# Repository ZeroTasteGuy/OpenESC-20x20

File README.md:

# OpenESC-20x20

A 4-in-1 sensorless BLDC ESC for the **20 x 20 mm** FPV stack hole pattern: four
independent motor controllers, each with its own MCU, gate driver and six
MOSFETs, running AM32 and taking DShot over a standard 8-pin connector.

> **Status: placement only.** All parts are placed, but there is **no copper and
> no routing**. The board has not been routed, fabricated or tested. Do not
> order it. See [Known issues](#known-issues).

3D views: [top](hardware-20x20/images/20x20-3d-top.png),
[bottom](hardware-20x20/images/20x20-3d-bottom.png).

This is a new PCB layout of the circuit from
[OpenDrone-hw/OpenESC-30x30](https://github.com/OpenDrone-hw/OpenESC-30x30)
(CERN-OHL-S-2.0, maintainer [@Just4Stan](https://github.com/Just4Stan)). The
outline and layout are new, and this board **does not include the current-sense
circuit** (see below); the schematic was edited to match. It is not an official
OpenDrone or Incutec release and is not covered by the upstream OSHWA
certification.

## What changed from the 30x30

| | 30x30 (upstream) | 20x20 (this layout) |
|---|---|---|
| Mounting holes | 30.5 mm pattern | 20 x 20 mm, 4 mm unplated, no copper ring |
| Board size | 30.5 mm class | about 35 x 42 mm including battery tab |
| Layers / copper | 6 layers, 1.6 mm, 2 oz outer / 1 oz inner | same (rules in `4in1.kicad_pro` and `4in1.kicad_dru`) |
| Motor pads | per upstream | corner groups, 3 pads per motor, no notch mid-edge |
| MOSFETs | 24 | 24, as 12 stacked pairs (high side top, low side bottom) |
| Bulk ceramic 1206 | 52 | **28**, on top near the MOSFETs |
| Battery pads | per upstream | two castellated pads on a tab, 4 mm wide x 1.5 mm deep |
| MCU, drivers, critical passives | per upstream | bottom side |
| Programming pads | per upstream | 2.54 mm pitch with hand-rework clearance |
| Current sense | INA186 + 2 shunts, board level | **not on this board** |

Fewer bulk capacitors means less local ripple filtering; install the 470 uF 50 V
electrolytic on the battery leads. Current capacity of this layout is **not**
validated; four channels at 60 A through a board this size is not realistic. See
[hardware-20x20/docs/DESIGN-NOTES.md](hardware-20x20/docs/DESIGN-NOTES.md).

## Specifications (circuit, as upstream)

| | |
|---|---|
| Firmware | AM32 |
| ESC protocol | DShot, bidirectional |
| Telemetry | Extended DShot |
| Input | 2-8S LiPo (6.0-33.6 V) |
| BEC | None |
| Rated current | 60 A / channel in the 30x30 design; **not established for this layout** |

## Architecture

Four independent channels share one power input and one connector. Per channel:
an **AT32F421G8U7** (Cortex-M4, QFN-28) drives an **NSG2065Q** three-phase
half-bridge gate driver, which drives six **SP40N01GHNK** MOSFETs, two per
phase. One channel is drawn once in `ESC.kicad_sch` and instantiated four times.

**There is no current sensing on this board.** The upstream design has a board-level
INA186A3IDCKR across two 0.2 mOhm shunts, reported as `/CURR`. That circuit is
not placed here and was removed from the schematic: U12, Rsense1, Rsense2, R89,
R90, C40, C41, C42, C94 and R73. No per-phase shunts were added either. The
battery pad (U3 pin 1) now connects straight to `+BATT`. `/CURR` (connector pin 3)
is kept as a net but is not driven.

## Power

```
Battery + (2S-8S) ─► +BATT
+BATT ─┬─► MOSFET drains, motor phases
       └─► LMR54406DBVR buck ─► +10V ─┬─► 4x gate driver
                                      └─► TLV76733DRVR ─► +3V3 ─► 4x MCU
```

## Key parts

| Function | Ref | Part | LCSC | Note |
|---|---|---|---|---|
| Motor MCU, x4 | U2, U5, U7, U9 | AT32F421G8U7, QFN-28 | C2765098 | One per channel |
| Gate driver, x4 | U4, U6, U8, U10 | NSG2065Q, QFN-24 | C41414478 | Standard footprint, alternatives exist |
| Power MOSFET, x24 | Q1-Q24 | SP40N01GHNK, PDFN-8L 5x6 | C22385416 | 40 V, 6 per channel; standard 5x6 DFN footprint |
| Buck | U13 | LMR54406DBVR, SOT-23-6 | C5219316 | 1.1 MHz, 0.6 A; FB 115k/10k against 0.8 V for 10.0 V out |
| Buck inductor | U14 | FTC160808S4R7MBCA | C46594347 | 4.7 uH |
| LDO | U15 | TLV76733DRVR, WSON-6 | C2848334 | +10 V to +3V3 |
| Connector | J1 | SM08B-SRSS-TB, JST SH 8-pin | C160407 | Also broken out as castellated pads |
| Bulk electrolytic | / | 470 uF 50 V | / | Installed by the user on the battery leads |
| Bulk ceramic | see PCB | 4.7 uF 1206, X5R 50 V | C380366 | 28 fitted on this layout |

## Connectors and I/O

Betaflight standard 8-pin:

| Pin | Net | Function |
|---|---|---|
| 1 | +BATT | Battery positive |
| 2 | GND | Ground |
| 3 | /CURR | Current sense output; **not driven on this board** (no INA186 fitted) |
| 4 | unconnected | See below |
| 5 | /M1 | DShot, channel 1 |
| 6 | /M2 | DShot, channel 2 |
| 7 | /M3 | DShot, channel 3 |
| 8 | /M4 | DShot, channel 4 |

Pin 4 is the dedicated telemetry pin in the Betaflight 8-pin standard and is
intentionally left unconnected: ESC to FC telemetry rides the motor signal lines
over bidirectional extended DShot instead.

## Layout rules

Bulk decoupling on +BATT and GND exists on the PCB without matching schematic
symbols. That is a deliberate board-only bank. Do not run update-from-schematic
without checking what it would delete.

## Firmware

[AM32](https://github.com/am32-firmware/AM32). Load the bootloader
(`AM32_F421_BOOTLOADER_PB4_V19.hex`) first with an ST-LINK, then flash and
configure the firmware in-browser at [am32.ca](https://am32.ca). Works with
Betaflight and any other DShot-capable flight controller.

## Repository

| | |
|---|---|
| Designed in | KiCad 10 |
| KiCad project | `hardware-20x20/4in1.kicad_pro` (name kept from upstream) |
| Schematics | `hardware-20x20/4in1.kicad_sch` (power, connectors, board block U3, castellated strip J2) plus `ESC.kicad_sch` (one channel, instantiated 4x, unchanged from upstream) |
| Board | `hardware-20x20/4in1.kicad_pcb`, 6 layers, 1.6 mm, 2 oz outer / 1 oz inner copper |
| Board setup | 0.09 mm clearance and track, 0.16 mm on outer layers (2 oz), via 0.35 on 0.20 drill |
| Design rules | `hardware-20x20/4in1.kicad_dru` |
| Local libraries | `components.kicad_sym`, `4in1ESC-30x30.pretty/`, `4in1ESC-30x30.3dshapes/` (only the models in use), inherited from upstream |
| Fab config | `hardware-20x20/fabrication-toolkit-options.json` |
| Renders | `hardware-20x20/images/` |
| Design notes | `hardware-20x20/docs/DESIGN-NOTES.md` |
| Last DRC | `hardware-20x20/docs/drc-v15-placement.json` |
| Placement scripts | `hardware-20x20/tools/` (provenance only, see its README) |
| License | CERN-OHL-S-2.0, see [LICENSE](LICENSE) |

## Checks

```sh
kicad-cli sch erc hardware-20x20/4in1.kicad_sch
kicad-cli pcb drc --schematic-parity --refill-zones hardware-20x20/4in1.kicad_pcb
```

Last DRC run (`docs/drc-v15-placement.json`, without schematic parity): no
clearance or annular-ring errors after the castellated pad fix (the project has
`copper_edge_clearance` set to ignore; with it on, 4 hits remain on the battery
tab, see `hardware-20x20/docs/DESIGN-NOTES.md`); 29
`lib_footprint_mismatch` (to be cleared by re-saving footprints from KiCad
against the local library); 472 unconnected items because nothing is routed.

With schematic parity and ERC (KiCad 10, run on this schematic and board):

- Parity: every schematic part is on the board, and J2 matches except for its
  value and BOM flag (see Known issues). 25 footprints are
  board-only (the CB bulk caps, kept board-only as upstream does). 16
  `net_conflict` notes on IC pads and a J2 pad 4 net name are inherited from
  upstream and the board's footprints. About 146 field mismatches are metadata
  only (Manufacturer fields blank on the board).
- ERC: 18 `pin_not_driven` errors (was 24 upstream) and 4
  `power_pin_not_driven` (was 3). Two of those four appeared because the removed
  U3 power-output pins no longer drive `+BATT` and `GND`; adding a PWR_FLAG on
  each net clears them.

KiCad files cannot be merged. Close KiCad before any scripted write to a KiCad
file, and do not text-edit `.kicad_sch`, `.kicad_pcb` or `.kicad_dru`.

## Known issues

- **Schematic edits to finish.** Add a PWR_FLAG on `+BATT` and `GND` to clear two
  new ERC errors, and set J2's value to "Castellated FC pads" with Exclude from
  BOM ticked so it matches the board footprint exactly.
- **No current sensing.** Removed on purpose (see Architecture). The ESC reports no
  current telemetry; `/CURR` is undriven.
- No copper, planes, vias or tracks. Routing, power-plane design and a current
  and thermal check are all still to do.
- The castellated pads need the fab to accept half-plated holes of this size.
- Some small parts sit in tight clusters (0.2 to 0.3 mm gaps). An earlier
  routing attempt on a related layout failed mostly on boxed-in pads, so expect
  to spread parts or route by hand.
- Silkscreen text may still carry upstream naming; review before any fab export.

## Revisions

| Rev | Date | Change |
|---|---|---|
| v15 | 2026-10-08 | Placement only: 28 bulk caps with fab-safe spacing, battery castellation pads run to the edge, J2 silk labels 1.0 mm. No copper. |
| v15a | 2026-10-08 | Castellated motor and signal pads widened to 5 mm (clears the annular-width DRC errors). Schematic matched to the board: current-sense circuit removed, castellated strip J2 added, U3 board block redrawn as the real outline with only the pins that have pads. |

Upstream revision history (30x30 Rev1 to Rev3.3) is in the
[OpenESC-30x30 repository](https://github.com/OpenDrone-hw/OpenESC-30x30).

## Credit and licence

CERN-OHL-S-2.0, same as upstream. Original circuit and 30x30 design by the
OpenDrone / Incutec team, maintainer @Just4Stan. The 20x20 board layout is a
modified version; changes are limited to PCB outline and placement as described
above. Upstream branding, badges and certification do not carry over to this
layout.

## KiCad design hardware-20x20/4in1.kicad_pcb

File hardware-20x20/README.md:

# OpenESC 20x20 layout (derivative of OpenESC-30x30)

An alternative PCB layout of the OpenESC-30x30 4-in-1 sensorless BLDC ESC for the
**20 x 20 mm** FPV stack hole pattern. The circuit is the upstream circuit; only
the board is new.

> **Status: placement only.** All parts are placed, but there is **no copper and
> no routing**. The board has not been routed, fabricated or tested. Do not order
> it. See [Known issues](#known-issues).

Derived from [OpenDrone-hw/OpenESC-30x30](https://github.com/OpenDrone-hw/OpenESC-30x30)
(CERN-OHL-S-2.0). This is not an official OpenDrone or Incutec release and is not
covered by the upstream OSHWA certification.

3D views: [top](images/20x20-3d-top.png), [bottom](images/20x20-3d-bottom.png).

## What is the same as the 30x30

Schematics (`4in1.kicad_sch`, `ESC.kicad_sch`), symbols, nets, parts and the
design rules file are **byte-identical** to `../hardware/`. Nothing in the circuit
changed: four AT32F421 + NSG2065Q channels, 24 SP40N01GHNK MOSFETs, board-level
INA186 current sense, LMR54406 buck and TLV76733 LDO, 8-pin Betaflight connector.
See the [root README](../README.md) and [AGENTS.md](../AGENTS.md) for the
architecture, key parts and I/O pinout.

## What is different

| | 30x30 (upstream) | 20x20 (this layout) |
|---|---|---|
| Mounting holes | 30.5 mm pattern | 20 x 20 mm, 4 mm unplated, no copper ring |
| Board size | See upstream | about 35 x 42 mm with battery tab |
| Layers / copper | 6 layers, 1.6 mm, 2 oz outer / 1 oz inner | same (rules in `4in1.kicad_pro`, `4in1.kicad_dru`) |
| Motor pads | per upstream | corner groups, 3 pads per motor, no notches mid-edge |
| MOSFETs | 24 | 24, as 12 stacked pairs (high side top, low side bottom) |
| Bulk ceramic 1206 | 52 | **28** on top, near the MOSFETs |
| Battery pads | per upstream | two castellated pads on a tab, 4 mm wide x 1.5 mm deep |
| MCU, drivers, critical passives | per upstream | bottom side |
| Programming pads | per upstream | 2.54 mm pitch with hand-rework clearance |

Fewer bulk capacitors than the 30x30 means less local ripple filtering; plan to
add the 470 uF electrolytic on the battery leads as the upstream README says.
Per-phase current capacity of the 20x20 layout has **not** been validated: four
channels at 60 A through a board this size is not realistic. See
[docs/DESIGN-NOTES.md](docs/DESIGN-NOTES.md).

## Files

| Path | Content |
|---|---|
| `4in1.kicad_pro`, `.kicad_pcb`, `.kicad_sch`, `ESC.kicad_sch` | KiCad 10 project (name kept from upstream) |
| `4in1.kicad_dru` | Fab design rules |
| `components.kicad_sym` | Local symbols (same as upstream) |
| `fp-lib-table`, `sym-lib-table` | Point at `../hardware/` for the footprint library and the `KiCad-Library` submodule, so nothing is duplicated |
| `fabrication-toolkit-options.json` | Fab export config (archive name still the 30x30 one, change before any export) |
| `images/` | Renders used above |
| `docs/DESIGN-NOTES.md` | Layout decisions, rules followed, findings |
| `docs/drc-v15-placement.json` | Last DRC run on this board |
| `tools/` | Scripts used to generate the placement (provenance only, see [tools/README.md](tools/README.md)) |

## Open the project

```sh
git clone --recurse-submodules <your fork url>
# open hardware-20x20/4in1.kicad_pro in KiCad 10
```

The `OpenDrone` libraries resolve through `../hardware/KiCad-Library`, so the
submodule must be checked out.

## Checks

```sh
kicad-cli sch erc hardware-20x20/4in1.kicad_sch
kicad-cli pcb drc --schematic-parity --refill-zones hardware-20x20/4in1.kicad_pcb
```

Last DRC (`docs/drc-v15-placement.json`): 0 clearance errors; 20 `annular_width`
(the castellated battery and motor pad half-holes, expected for castellation),
29 `lib_footprint_mismatch` (library table path differs from where the footprints
were copied from, to be re-saved from KiCad), and 472 unconnected items because
nothing is routed. ERC was not re-run for this layout; the schematic is unchanged
from upstream.

## Known issues

- No copper, planes, vias or tracks. Routing, power-plane design and a current
  and thermal check are all still to do.
- The 20 castellation `annular_width` findings need the fab to accept
  half-plated holes of this size.
- Some small parts sit in tight clusters (0.2 to 0.3 mm gaps). An earlier
  routing attempt on a related layout failed mostly on boxed-in pads, so expect
  to spread parts or route by hand.
- Silkscreen and `fabrication-toolkit-options.json` still carry upstream naming.

## Licence and credit

CERN-OHL-S-2.0, same as upstream (see [../LICENSE](../LICENSE)). Original design
by the OpenDrone / Incutec team, maintainer @Just4Stan. The 20x20 layout in this
folder is a modified version; changes are limited to PCB placement and outline
as described above.

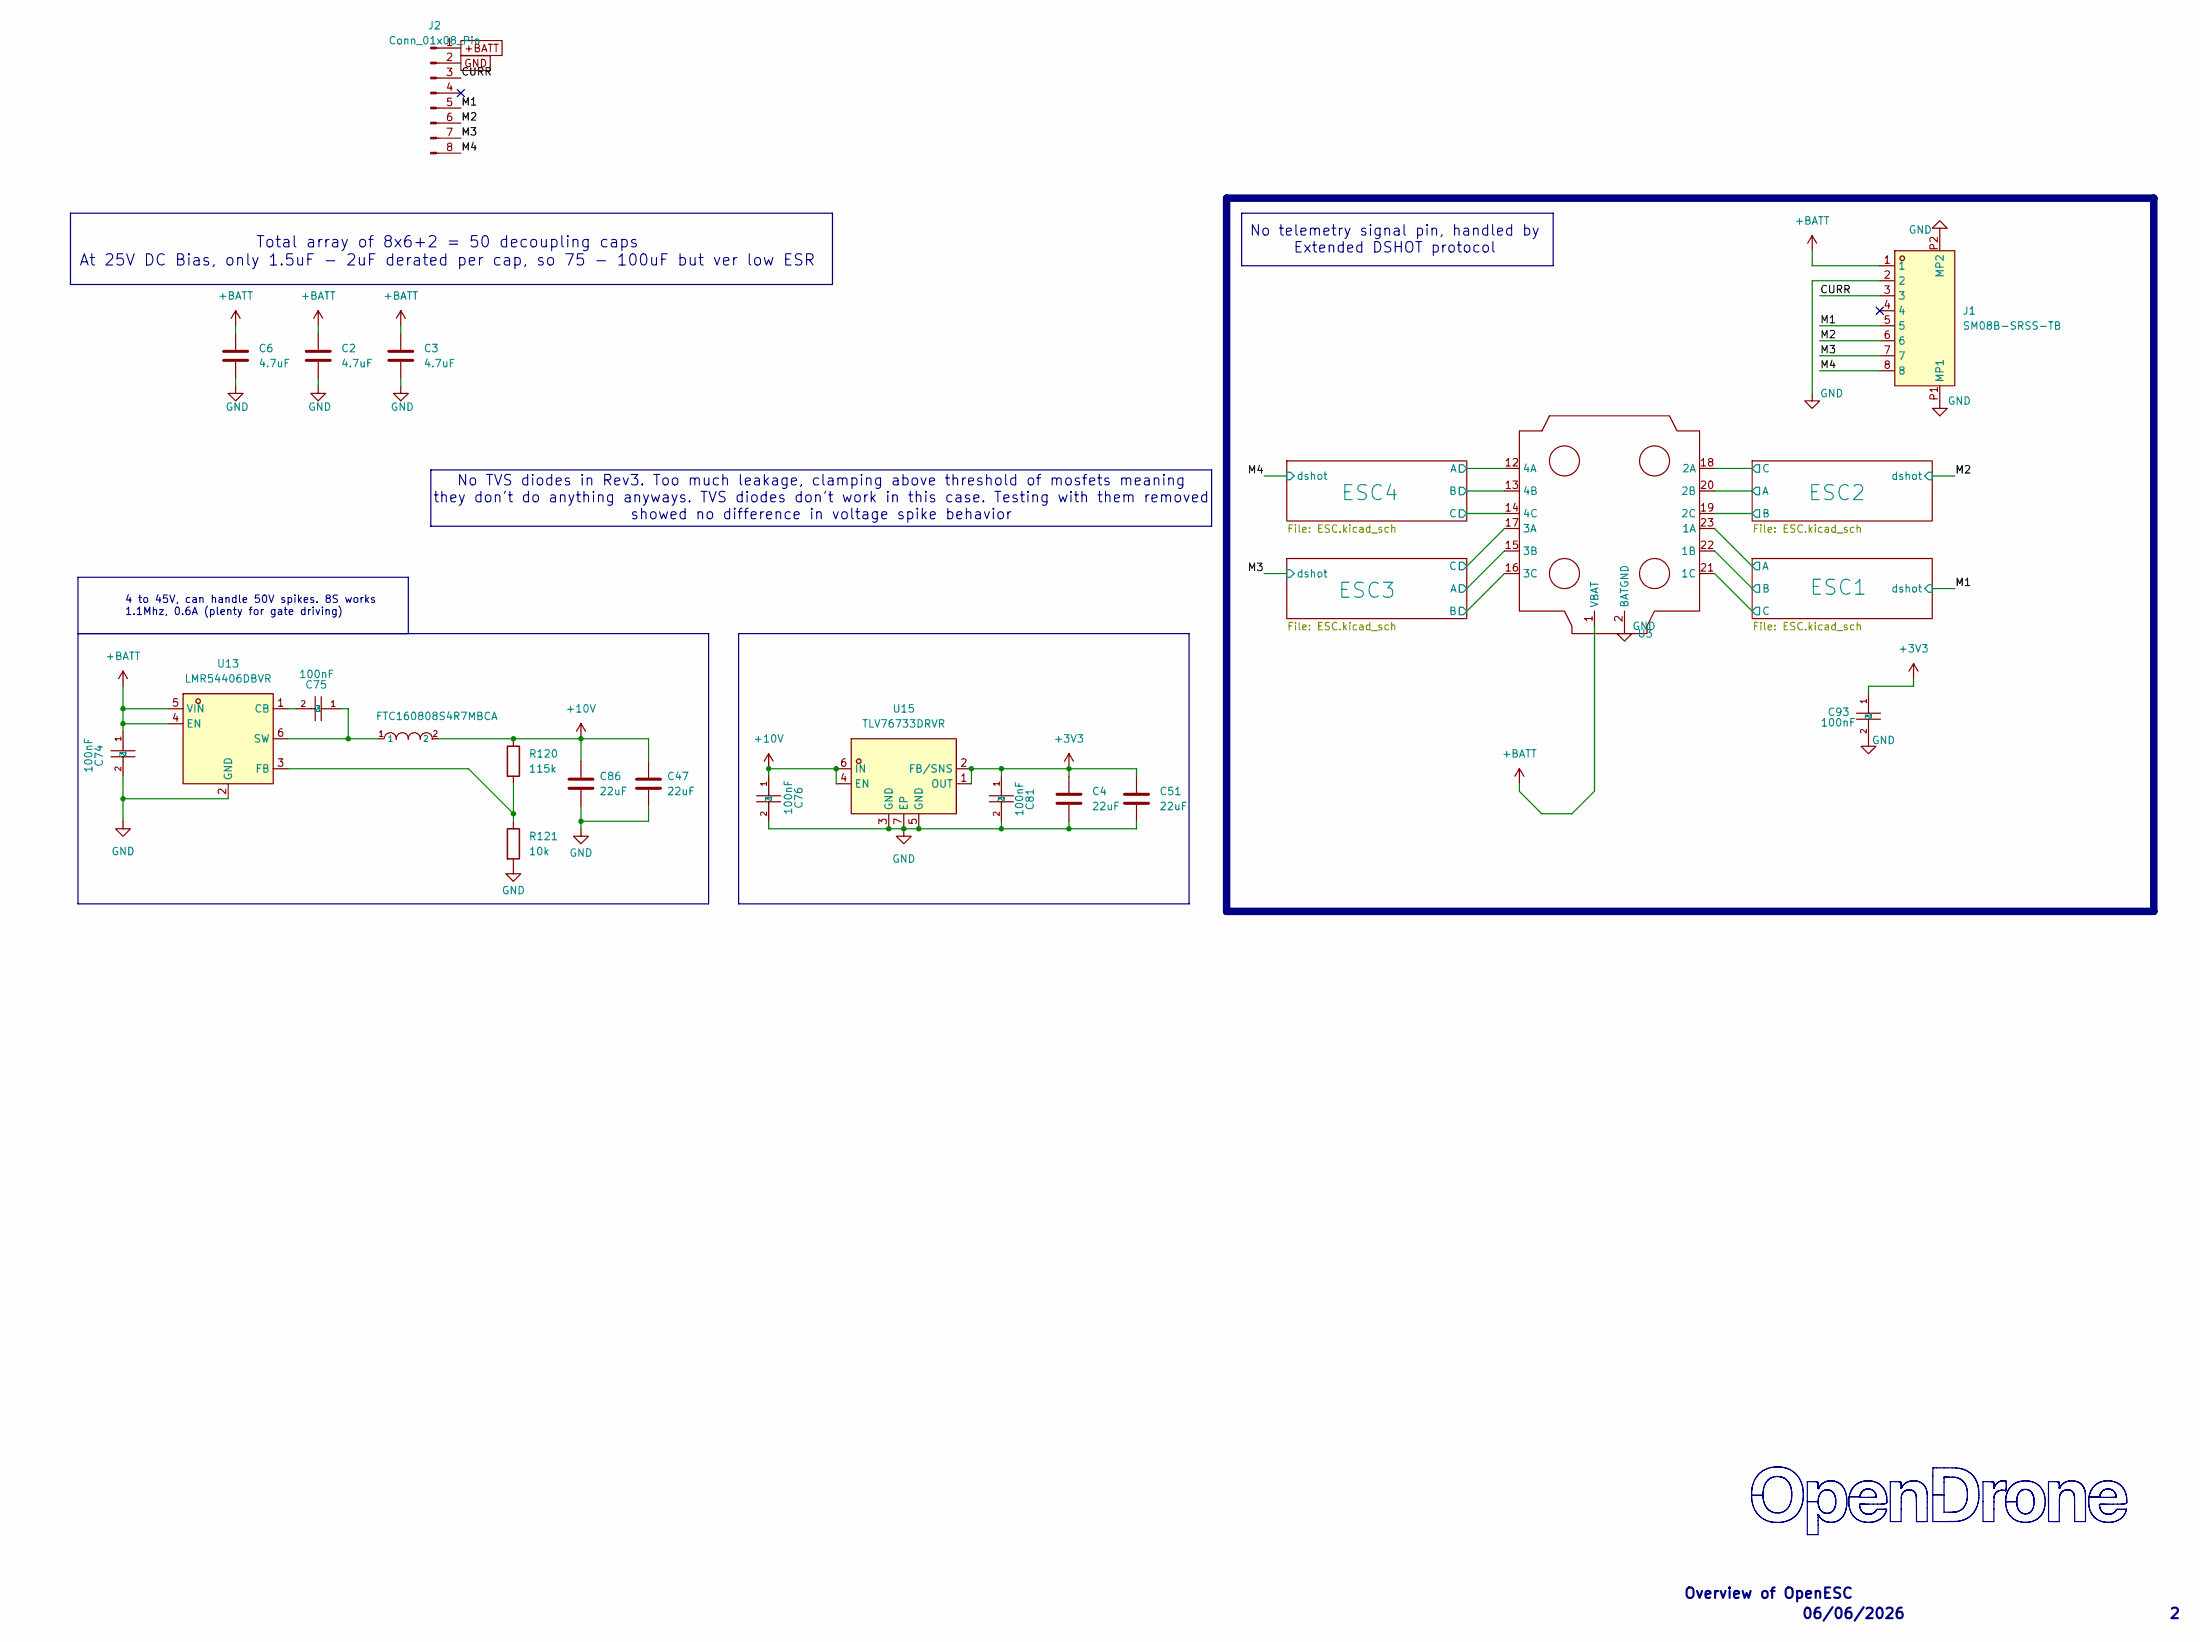
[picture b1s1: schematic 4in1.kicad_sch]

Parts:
C2, C3, C6: 4.7uF; C_1206_3216Metric; MPN TCC1206X7R475K500HT; LCSC C380366
C4, C51: 22uF; C_0402_1005Metric; MPN CL05A226MQ5QUNC; LCSC C105226
C47, C86: 22uF; C_0603_1608Metric; MPN CL10A226MO7JZNC; LCSC C2762594
C74, C75, C76, C81, C93: 100nF; C_0201_0603Metric; MPN GRM033R6YA104KE14D; LCSC C181043
J1: SM08B-SRSS-TB; JST_SM08B-SRSS-TB; MPN SM08B-SRSS-TB(LF)(SN); LCSC C160407
J2: Conn_01x08_Pin; Castellated_8x1.50
R120: 115k; R_0201_0603Metric; MPN RTT011153FTH; LCSC C166378
R121: 10k; R_0201_0603Metric; MPN RC0201FR-0710KL; LCSC C106225
U3: 4in1ESC30x30
U13: LMR54406DBVR; SOT-23-6_L2.9-W1.6-P0.95-LS2.8-BR; MPN LMR54406DBVR; LCSC Part C5219316
U14: FTC160808S4R7MBCA; IND-SMD_L1.6-W0.8_FTC160865SR47MBCA; MPN FTC160808S4R7MBCA; LCSC C46594347
U15: TLV76733DRVR; WSON-6_L2.0-W2.0-P0.65-TL-EP; MPN TLV76733DRVR; LCSC C2848334

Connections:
+3V3: C4.2, C51.2, C81.1, C93.1, U15.1 (OUT), U15.2 (FB/SNS); also elsewhere on the board
+10V: C47.1, C76.1, C86.1, R120.1, U14.2, U15.4 (EN), U15.6 (IN); also elsewhere on the board
+BATT: C2.1, C3.1, C6.1, C74.1, J1.1, J2.1 (VCC), U3.1 (VBAT), U13.4 (EN), U13.5 (VIN); also elsewhere on the board
/CURR: J1.3, J2.3 (CUR)
/ESC1/MotorA: U3.23 (1A); also elsewhere on the board
/ESC1/MotorB: U3.22 (1B); also elsewhere on the board
/ESC1/MotorC: U3.21 (1C); also elsewhere on the board
/ESC2/MotorA: U3.20 (2B); also elsewhere on the board
/ESC2/MotorB: U3.19 (2C); also elsewhere on the board
/ESC2/MotorC: U3.18 (2A); also elsewhere on the board
/ESC3/MotorA: U3.15 (3B); also elsewhere on the board
/ESC3/MotorB: U3.16 (3C); also elsewhere on the board
/ESC3/MotorC: U3.17 (3A); also elsewhere on the board
/ESC4/MotorA: U3.12 (4A); also elsewhere on the board
/ESC4/MotorB: U3.13 (4B); also elsewhere on the board
/ESC4/MotorC: U3.14 (4C); also elsewhere on the board
/M1: J1.5, J2.5 (S1); also elsewhere on the board
/M2: J1.6, J2.6 (S2); also elsewhere on the board
/M3: J1.7, J2.7 (S3); also elsewhere on the board
/M4: J1.8, J2.8 (S4); also elsewhere on the board
GND: C2.2, C3.2, C4.1, C6.2, C47.2, C51.1, C74.2, C76.2, C81.2, C86.2, C93.2, J1.2, J1.P1 (MP1), J1.P2 (MP2), J2.2 (GND), R121.2, U3.2 (BATGND), U13.2 (GND), U15.3 (GND), U15.5 (GND), U15.7 (EP); also elsewhere on the board
unnamed: C75.2, U13.1 (CB)
unnamed: R120.2, R121.1, U13.3 (FB)
unnamed: C75.1, U13.6 (SW), U14.1

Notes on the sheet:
No telemetry signal pin, handled by Extended DSHOT protocol
Overview of OpenESC
No TVS diodes in Rev3. Too much leakage, clamping above threshold of mosfets meaning they don't do anything anyways. TVS diodes don't work in this case. Testing with them removed showed no difference in voltage spike behavior
06/06/2026
Total array of 8x6+2 = 50 decoupling caps At 25V DC Bias, only 1.5uF - 2uF derated per cap, so 75 - 100uF but ver low ESR
4 to 45V, can handle 50V spikes. 8S works 1.1Mhz, 0.6A (plenty for gate driving)

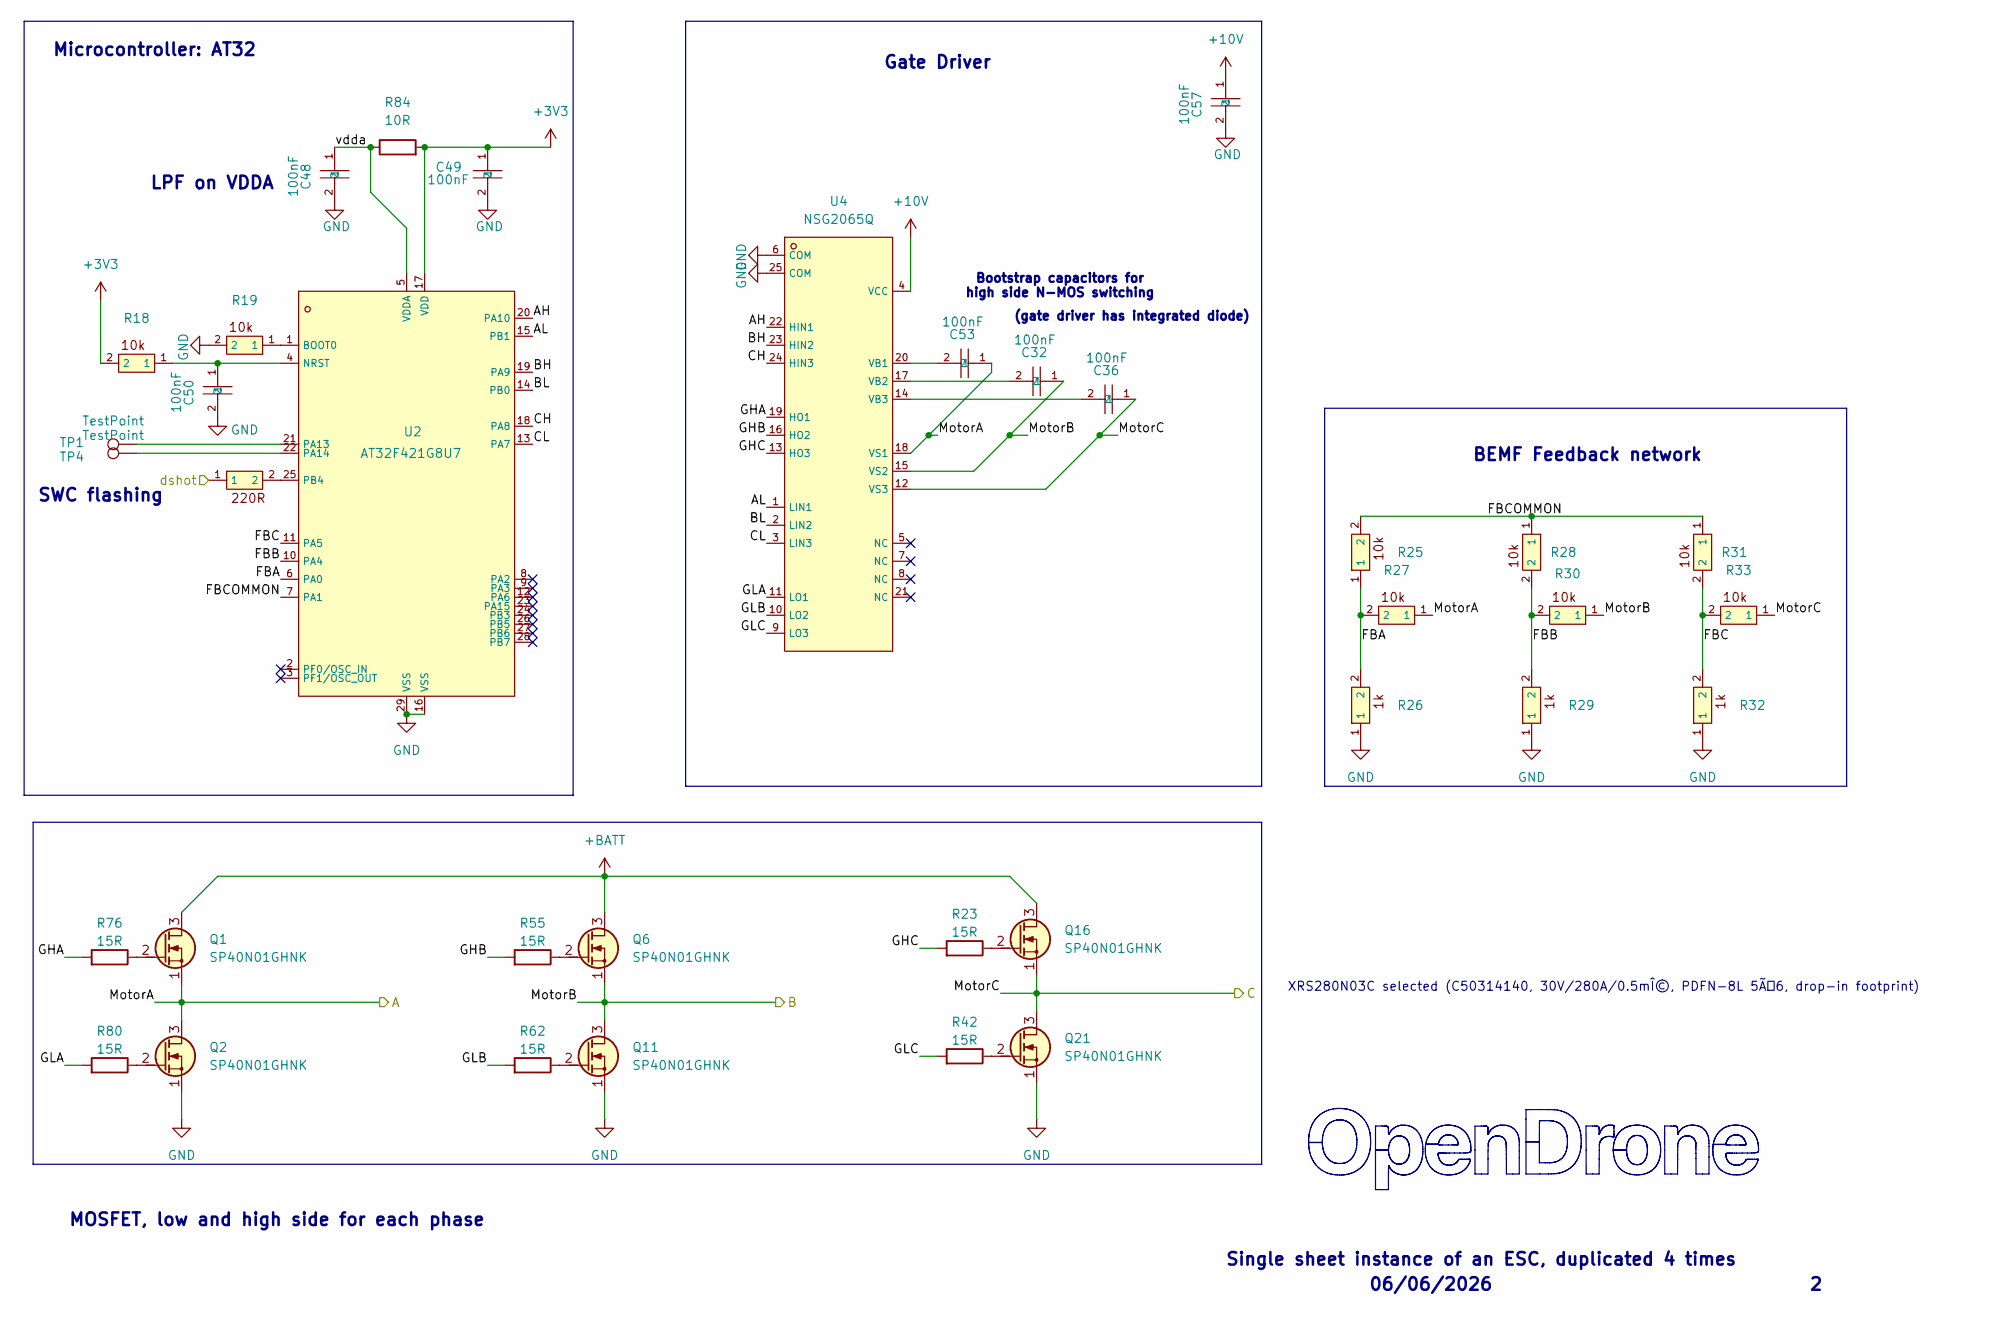
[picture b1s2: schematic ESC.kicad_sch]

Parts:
C32, C36, C53: 100nF; C_0402_WIDE; MPN CL05B104KB54PNC; LCSC C307331
C48, C49, C50, C57: 100nF; C_0201_0603Metric; MPN GRM033R6YA104KE14D; LCSC C181043
Q1, Q2, Q6, Q11, Q16, Q21: SP40N01GHNK; PDFN-8L_L6.0-W5.0-P1.27; MPN SP40N01GHNK; LCSC C22385416
R18, R19: 10k; R_0201_0603Metric; MPN RC0201FR-0710KL; LCSC C106225
R20: 220R; R_0201_0603Metric; MPN AC0201FR-07220RL; LCSC C226468
R23, R42, R55, R62, R76, R80: 15R; R_0201_0603Metric; MPN 0201WMF150JTEE; LCSC C473542
R25, R27, R28, R30, R31, R33: 10k; C_0201_0603Metric; MPN RC0201FR-0710KL; LCSC C106225
R26, R29, R32: 1k; C_0201_0603Metric; MPN 0201WMF1001TEE; LCSC C270365
R84: 10R; R_0201_0603Metric; MPN RC0201FR-0710RL; LCSC C106226
TP1, TP4: TestPoint; TestPoint_Pad_D1.0mm
U2: AT32F421G8U7; QFN-28_L4.0-W4.0-P0.40-TL-EP2.4; MPN AT32F421G8U7; LCSC C2765098
U4: NSG2065Q; QFN-24_L4.0-W4.0-P0.50-TL-EP2.8; MPN NSG2065Q; LCSC C41414478

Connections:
+3V3: C49.1, R18.2, R84.2, U2.17 (VDD); also elsewhere on the board
+10V: C57.1, U4.4 (VCC); also elsewhere on the board
+BATT: Q1.3 (D), Q6.3 (D), Q16.3 (D); also elsewhere on the board
/ESC1/AH: U2.20 (PA10), U4.22 (HIN1)
/ESC1/AL: U2.15 (PB1), U4.1 (LIN1)
/ESC1/BH: U2.19 (PA9), U4.23 (HIN2)
/ESC1/BL: U2.14 (PB0), U4.2 (LIN2)
/ESC1/CH: U2.18 (PA8), U4.24 (HIN3)
/ESC1/CL: U2.13 (PA7), U4.3 (LIN3)
/ESC1/FBA: R25.1, R26.2, R27.2, U2.6 (PA0)
/ESC1/FBB: R28.2, R29.2, R30.2, U2.10 (PA4)
/ESC1/FBC: R31.2, R32.2, R33.2, U2.11 (PA5)
/ESC1/FBCOMMON: R25.2, R28.1, R31.1, U2.7 (PA1)
/ESC1/GHA: R76.1, U4.19 (HO1)
/ESC1/GHB: R55.1, U4.16 (HO2)
/ESC1/GHC: R23.1, U4.13 (HO3)
/ESC1/GLA: R80.1, U4.11 (LO1)
/ESC1/GLB: R62.1, U4.10 (LO2)
/ESC1/GLC: R42.1, U4.9 (LO3)
/ESC1/MotorA: C53.1, Q1.1 (S), Q2.3 (D), R27.1, U4.18 (VS1); also elsewhere on the board
/ESC1/MotorB: C32.1, Q6.1 (S), Q11.3 (D), R30.1, U4.15 (VS2); also elsewhere on the board
/ESC1/MotorC: C36.1, Q16.1 (S), Q21.3 (D), R33.1, U4.12 (VS3); also elsewhere on the board
/ESC1/vdda: C48.1, R84.1, U2.5 (VDDA)
/M1: R20.1; also elsewhere on the board
GND: C48.2, C49.2, C50.2, C57.2, Q2.1 (S), Q11.1 (S), Q21.1 (S), R19.2, R26.1, R29.1, R32.1, U2.16 (VSS), U2.29 (VSS), U4.6 (COM), U4.25 (COM); also elsewhere on the board
unnamed: Q1.2 (G), R76.2
unnamed: Q2.2 (G), R80.2
unnamed: Q6.2 (G), R55.2
unnamed: Q11.2 (G), R62.2
unnamed: Q16.2 (G), R23.2
unnamed: Q21.2 (G), R42.2
unnamed: R19.1, U2.1 (BOOT0)
unnamed: C50.1, R18.1, U2.4 (NRST)
unnamed: TP1.1 (1_1), U2.21 (PA13)
unnamed: TP4.1 (1_1), U2.22 (PA14)
unnamed: R20.2, U2.25 (PB4)
unnamed: C53.2, U4.20 (VB1)
unnamed: C32.2, U4.17 (VB2)
unnamed: C36.2, U4.14 (VB3)

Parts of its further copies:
C33, C34, C35, C37, C38, C39, C56, C62, C67: 100nF; C_0402_WIDE; MPN CL05B104KB54PNC; LCSC C307331
C52, C54, C55, C58, C59, C60, C61, C63, C64, C65, C66, C68: 100nF; C_0201_0603Metric; MPN GRM033R6YA104KE14D; LCSC C181043
Q3, Q4, Q5, Q7, Q8, Q9, Q10, Q12, Q13, Q14, Q15, Q17, Q18, Q19, Q20, Q22, Q23, Q24: SP40N01GHNK; PDFN-8L_L6.0-W5.0-P1.27; MPN SP40N01GHNK; LCSC C22385416
R10, R12, R13, R15, R34, R36, R46, R48, R49, R51, R52, R54, R64, R66, R67, R69, R70, R72: 10k; C_0201_0603Metric; MPN RC0201FR-0710KL; LCSC C106225
R11, R14, R35, R47, R50, R53, R65, R68, R71: 1k; C_0201_0603Metric; MPN 0201WMF1001TEE; LCSC C270365
R21, R22, R40, R41, R58, R59: 10k; R_0201_0603Metric; MPN RC0201FR-0710KL; LCSC C106225
R24, R37, R38, R43, R44, R45, R56, R60, R61, R63, R74, R75, R77, R78, R79, R81, R82, R83: 15R; R_0201_0603Metric; MPN 0201WMF150JTEE; LCSC C473542
R39, R57, R87: 220R; R_0201_0603Metric; MPN AC0201FR-07220RL; LCSC C226468
R85, R86, R88: 10R; R_0201_0603Metric; MPN RC0201FR-0710RL; LCSC C106226
TP2, TP3, TP5, TP6, TP7, TP8: TestPoint; TestPoint_Pad_D1.0mm
U5, U7, U9: AT32F421G8U7; QFN-28_L4.0-W4.0-P0.40-TL-EP2.4; MPN AT32F421G8U7; LCSC C2765098
U6, U8, U10: NSG2065Q; QFN-24_L4.0-W4.0-P0.50-TL-EP2.8; MPN NSG2065Q; LCSC C41414478

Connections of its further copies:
+3V3: C55.1, C61.1, C66.1, R21.2, R40.2, R58.2, R85.2, R86.2, R88.2, U5.17 (VDD), U7.17 (VDD), U9.17 (VDD); also elsewhere on the board
+10V: C58.1, C63.1, C68.1, U6.4 (VCC), U8.4 (VCC), U10.4 (VCC); also elsewhere on the board
+BATT: Q7.3 (D), Q8.3 (D), Q9.3 (D), Q10.3 (D), Q13.3 (D), Q17.3 (D), Q18.3 (D), Q19.3 (D), Q20.3 (D); also elsewhere on the board
/ESC2/AH: U5.20 (PA10), U6.22 (HIN1)
/ESC2/AL: U5.15 (PB1), U6.1 (LIN1)
/ESC2/BH: U5.19 (PA9), U6.23 (HIN2)
/ESC2/BL: U5.14 (PB0), U6.2 (LIN2)
/ESC2/CH: U5.18 (PA8), U6.24 (HIN3)
/ESC2/CL: U5.13 (PA7), U6.3 (LIN3)
/ESC2/FBA: R10.1, R11.2, R12.2, U5.6 (PA0)
/ESC2/FBB: R13.2, R14.2, R15.2, U5.10 (PA4)
/ESC2/FBC: R34.2, R35.2, R36.2, U5.11 (PA5)
/ESC2/FBCOMMON: R10.2, R13.1, R34.1, U5.7 (PA1)
/ESC2/GHA: R77.1, U6.19 (HO1)
/ESC2/GHB: R56.1, U6.16 (HO2)
/ESC2/GHC: R24.1, U6.13 (HO3)
/ESC2/GLA: R81.1, U6.11 (LO1)
/ESC2/GLB: R63.1, U6.10 (LO2)
/ESC2/GLC: R43.1, U6.9 (LO3)
/ESC2/MotorA: C56.1, Q3.3 (D), Q7.1 (S), R12.1, U6.18 (VS1); also elsewhere on the board
/ESC2/MotorB: C33.1, Q8.1 (S), Q12.3 (D), R15.1, U6.15 (VS2); also elsewhere on the board
/ESC2/MotorC: C37.1, Q17.1 (S), Q22.3 (D), R36.1, U6.12 (VS3); also elsewhere on the board
/ESC2/vdda: C54.1, R85.1, U5.5 (VDDA)
/ESC3/AH: U7.20 (PA10), U8.22 (HIN1)
/ESC3/AL: U7.15 (PB1), U8.1 (LIN1)
/ESC3/BH: U7.19 (PA9), U8.23 (HIN2)
/ESC3/BL: U7.14 (PB0), U8.2 (LIN2)
/ESC3/CH: U7.18 (PA8), U8.24 (HIN3)
/ESC3/CL: U7.13 (PA7), U8.3 (LIN3)
/ESC3/FBA: R46.1, R47.2, R48.2, U7.6 (PA0)
/ESC3/FBB: R49.2, R50.2, R51.2, U7.10 (PA4)
/ESC3/FBC: R52.2, R53.2, R54.2, U7.11 (PA5)
/ESC3/FBCOMMON: R46.2, R49.1, R52.1, U7.7 (PA1)
/ESC3/GHA: R78.1, U8.19 (HO1)
/ESC3/GHB: R60.1, U8.16 (HO2)
/ESC3/GHC: R37.1, U8.13 (HO3)
/ESC3/GLA: R82.1, U8.11 (LO1)
/ESC3/GLB: R74.1, U8.10 (LO2)
/ESC3/GLC: R44.1, U8.9 (LO3)
/ESC3/MotorA: C62.1, Q4.3 (D), Q13.1 (S), R48.1, U8.18 (VS1); also elsewhere on the board
/ESC3/MotorB: C34.1, Q9.1 (S), Q14.3 (D), R51.1, U8.15 (VS2); also elsewhere on the board
/ESC3/MotorC: C38.1, Q18.1 (S), Q23.3 (D), R54.1, U8.12 (VS3); also elsewhere on the board
/ESC3/vdda: C60.1, R86.1, U7.5 (VDDA)
/ESC4/AH: U9.20 (PA10), U10.22 (HIN1)
/ESC4/AL: U9.15 (PB1), U10.1 (LIN1)
/ESC4/BH: U9.19 (PA9), U10.23 (HIN2)
/ESC4/BL: U9.14 (PB0), U10.2 (LIN2)
/ESC4/CH: U9.18 (PA8), U10.24 (HIN3)
/ESC4/CL: U9.13 (PA7), U10.3 (LIN3)
/ESC4/FBA: R64.1, R65.2, R66.2, U9.6 (PA0)
/ESC4/FBB: R67.2, R68.2, R69.2, U9.10 (PA4)
/ESC4/FBC: R70.2, R71.2, R72.2, U9.11 (PA5)
/ESC4/FBCOMMON: R64.2, R67.1, R70.1, U9.7 (PA1)
/ESC4/GHA: R79.1, U10.19 (HO1)
/ESC4/GHB: R61.1, U10.16 (HO2)
/ESC4/GHC: R38.1, U10.13 (HO3)
/ESC4/GLA: R83.1, U10.11 (LO1)
/ESC4/GLB: R75.1, U10.10 (LO2)
/ESC4/GLC: R45.1, U10.9 (LO3)
/ESC4/MotorA: C67.1, Q5.3 (D), Q19.1 (S), R66.1, U10.18 (VS1); also elsewhere on the board
/ESC4/MotorB: C35.1, Q10.1 (S), Q15.3 (D), R69.1, U10.15 (VS2); also elsewhere on the board
/ESC4/MotorC: C39.1, Q20.1 (S), Q24.3 (D), R72.1, U10.12 (VS3); also elsewhere on the board
/ESC4/vdda: C65.1, R88.1, U9.5 (VDDA)
/M2: R39.1; also elsewhere on the board
/M3: R57.1; also elsewhere on the board
/M4: R87.1; also elsewhere on the board
GND: C52.2, C54.2, C55.2, C58.2, C59.2, C60.2, C61.2, C63.2, C64.2, C65.2, C66.2, C68.2, Q3.1 (S), Q4.1 (S), Q5.1 (S), Q12.1 (S), Q14.1 (S), Q15.1 (S), Q22.1 (S), Q23.1 (S), Q24.1 (S), R11.1, R14.1, R22.2, R35.1, R41.2, R47.1, R50.1, R53.1, R59.2, R65.1, R68.1, R71.1, U5.16 (VSS), U5.29 (VSS), U6.6 (COM), U6.25 (COM), U7.16 (VSS), U7.29 (VSS), U8.6 (COM), U8.25 (COM), U9.16 (VSS), U9.29 (VSS), U10.6 (COM), U10.25 (COM); also elsewhere on the board
unnamed: Q3.2 (G), R81.2
unnamed: Q4.2 (G), R82.2
unnamed: Q5.2 (G), R83.2
unnamed: Q7.2 (G), R77.2
unnamed: Q8.2 (G), R56.2
unnamed: Q9.2 (G), R60.2
unnamed: Q10.2 (G), R61.2
unnamed: Q12.2 (G), R63.2
unnamed: Q13.2 (G), R78.2
unnamed: Q14.2 (G), R74.2
unnamed: Q15.2 (G), R75.2
unnamed: Q17.2 (G), R24.2
unnamed: Q18.2 (G), R37.2
unnamed: Q19.2 (G), R79.2
unnamed: Q20.2 (G), R38.2
unnamed: Q22.2 (G), R43.2
unnamed: Q23.2 (G), R44.2
unnamed: Q24.2 (G), R45.2
unnamed: R22.1, U5.1 (BOOT0)
unnamed: C52.1, R21.1, U5.4 (NRST)
unnamed: TP2.1 (1_1), U5.21 (PA13)
unnamed: TP5.1 (1_1), U5.22 (PA14)
unnamed: R39.2, U5.25 (PB4)
unnamed: C56.2, U6.20 (VB1)
unnamed: C33.2, U6.17 (VB2)
unnamed: C37.2, U6.14 (VB3)
unnamed: R41.1, U7.1 (BOOT0)
unnamed: C59.1, R40.1, U7.4 (NRST)
unnamed: TP3.1 (1_1), U7.21 (PA13)
unnamed: TP6.1 (1_1), U7.22 (PA14)
unnamed: R57.2, U7.25 (PB4)
unnamed: C62.2, U8.20 (VB1)
unnamed: C34.2, U8.17 (VB2)
unnamed: C38.2, U8.14 (VB3)
unnamed: R59.1, U9.1 (BOOT0)
unnamed: C64.1, R58.1, U9.4 (NRST)
unnamed: TP7.1 (1_1), U9.21 (PA13)
unnamed: TP8.1 (1_1), U9.22 (PA14)
unnamed: R87.2, U9.25 (PB4)
unnamed: C67.2, U10.20 (VB1)
unnamed: C35.2, U10.17 (VB2)
unnamed: C39.2, U10.14 (VB3)

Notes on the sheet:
Single sheet instance of an ESC, duplicated 4 times
MOSFET, low and high side for each phase
Gate Driver
SWC flashing
XRS280N03C selected (C50314140, 30V/280A/0.5mÎ©, PDFN-8L 5Ã6, drop-in footprint)
Bootstrap capacitors for high side N-MOS switching
BEMF Feedback network
(gate driver has integrated diode)
Microcontroller: AT32
LPF on VDDA
06/06/2026

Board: 6 copper layers, 189 parts (115 on the bottom side), 148 nets, no tracks yet.

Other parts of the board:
CB1, CB2, CB3, CB4, CB5, CB6, CB7, CB8, CB9, CB10, CB11, CB12, CB13, CB15, CB19, CB20, CB21, CB25, CB26, CB28, CB29, CB30, CB31, CB32, CB33: 4.7uF; C_1206_3216Metric

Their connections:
+BATT: CB1.1, CB2.1, CB3.1, CB4.1, CB5.1, CB6.1, CB7.1, CB8.1, CB9.1, CB10.1, CB11.1, CB12.1, CB13.1, CB15.1, CB19.1, CB20.1, CB21.1, CB25.1, CB26.1, CB28.1, CB29.1, CB30.1, CB31.1, CB32.1, CB33.1; also elsewhere on the board
GND: CB1.2, CB2.2, CB3.2, CB4.2, CB5.2, CB6.2, CB7.2, CB8.2, CB9.2, CB10.2, CB11.2, CB12.2, CB13.2, CB15.2, CB19.2, CB20.2, CB21.2, CB25.2, CB26.2, CB28.2, CB29.2, CB30.2, CB31.2, CB32.2, CB33.2; also elsewhere on the board
